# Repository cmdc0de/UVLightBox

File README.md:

# UVLightBox
UBLight Box with WIFI capabilities

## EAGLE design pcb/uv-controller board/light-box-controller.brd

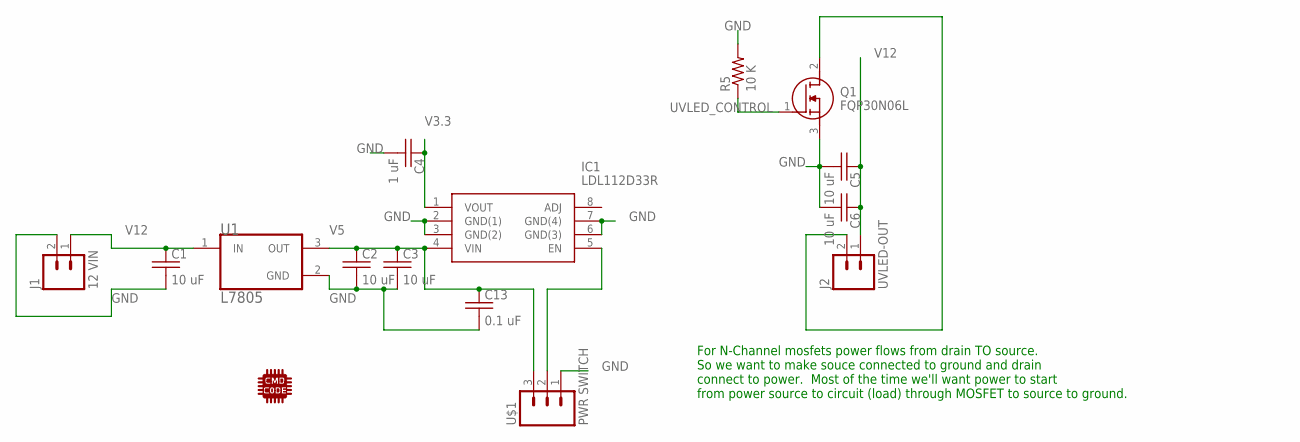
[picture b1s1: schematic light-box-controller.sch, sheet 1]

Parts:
C1, C2, C3, C5, C6: 10 uF; C0805K
C4: 1 uF; C0805K
C13: 0.1 uF; C0805K
IC1: LDL112D33R; SOIC127P600X175-8N
J1: 12 VIN; SCREWTERMINAL-5MM-2
J2: UVLED-OUT; SCREWTERMINAL-5MM-2
Q1: FQP30N06L; TO254P470X1016X2019-3P
R5: 10 K; 0805
U1: L7805; TO-220-3
U$1: PWR SWITCH; 1X03_LONGPADS
U$4: CMD_C0DE_LOGOCMD_CODE_LOGO_SILK; CMD_C0DE_LOGO_SILK

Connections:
GND: C1.2, C2.2, C3.2, C4.2, C5.2, C6.2, C13.2, IC1.2 (GND(1)), IC1.3 (GND(2)), IC1.6 (GND(3)), IC1.7 (GND(4)), J1.2, Q1.3 (S), R5.2, U1.2 (GND), U$1.1; also elsewhere on the board
unnamed: J2.2, Q1.2 (D)
unnamed: IC1.5 (EN), U$1.2
UVLED_CONTROL: Q1.1 (G), R5.1; also elsewhere on the board
V3.3: C4.1, IC1.1 (VOUT); also elsewhere on the board
V5: C2.1, C3.1, C13.1, IC1.4 (VIN), U1.3 (OUT), U$1.3
V12: C1.1, C5.1, C6.1, J1.1, J2.1, U1.1 (IN)

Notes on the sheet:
For N-Channel mosfets power flows from drain TO source. So we want to make souce connected to ground and drain connect to power. Most of the time we'll want power to start from power source to circuit (load) through MOSFET to source to ground.

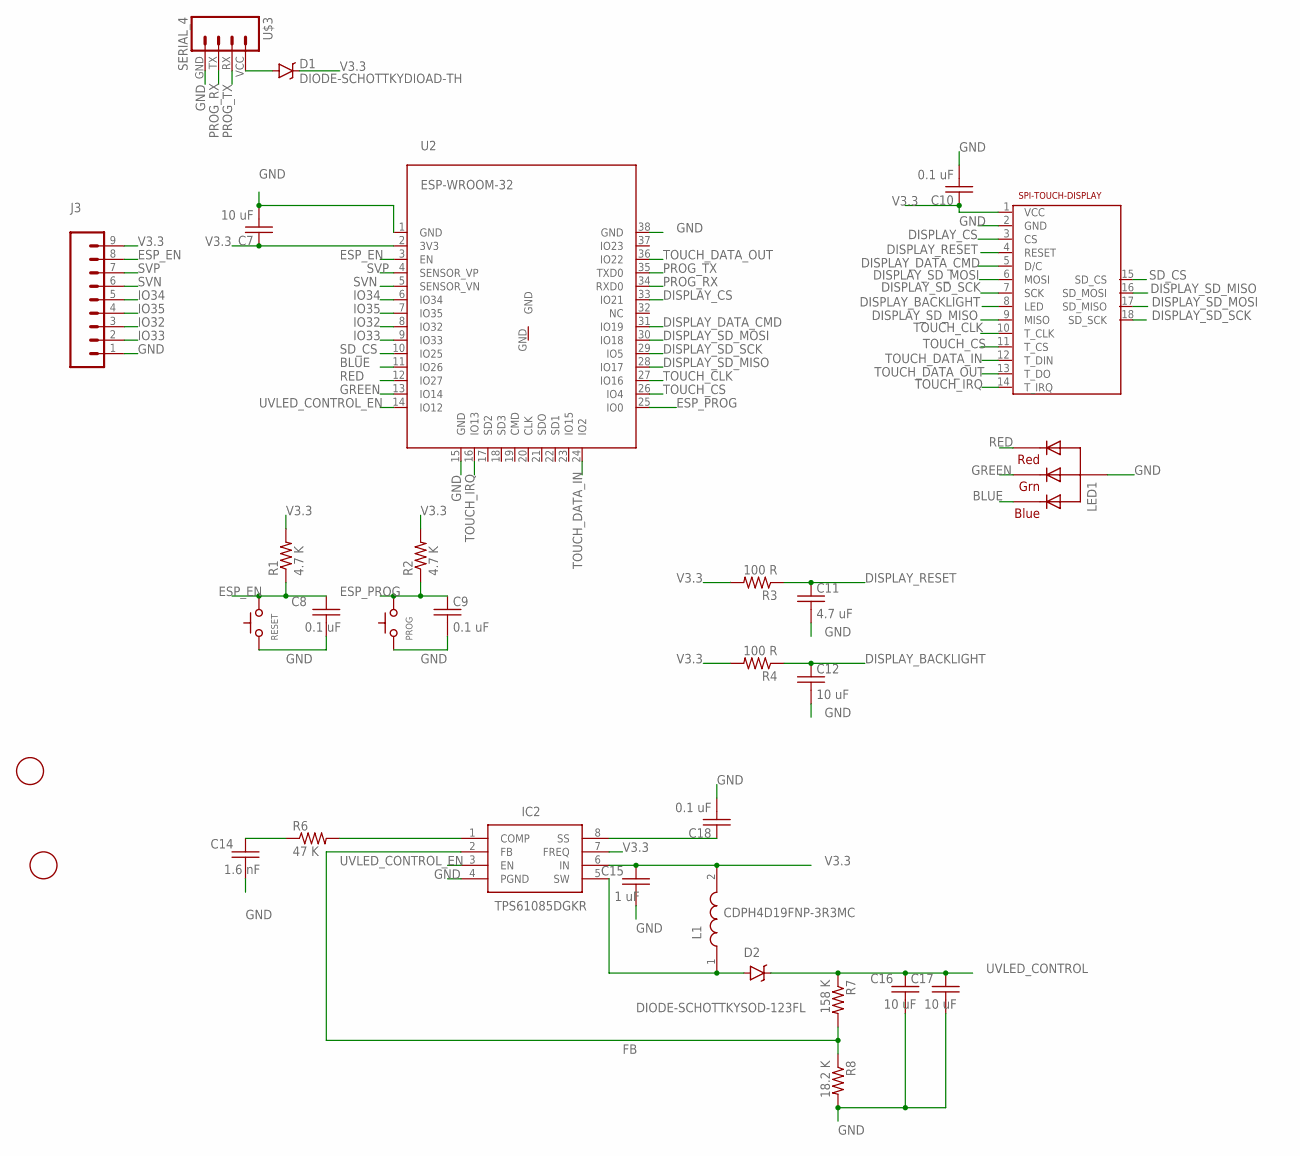
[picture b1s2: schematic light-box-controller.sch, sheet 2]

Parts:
C7, C12, C16, C17: 10 uF; C0805K
C8, C9, C10, C18: 0.1 uF; C0805K
C11: 4.7 uF; C0805K
C14: 1.6 nF; C0805K
C15: 1 uF; C0805K
D1: DIODE-SCHOTTKYDIOAD-TH; DIOAD1060W80L520D270
D2: DIODE-SCHOTTKYSOD-123FL; SOD-123FL
IC2: TPS61085DGKR; SOP65P490X110-8N
J3: M09LONGPADS; 1X09_LONGPADS
L1: CDPH4D19FNP-3R3MC; CDPH4D19FNP3R3MC
LED1: RGBLED_CA-PIRANHA; PIRANHA5MM
PROG: SWITCH_TACTILETACTILE-2PIN-NARROW; TACTILE-2PIN-NARROW
R1, R2: 4.7 K; 0805
R3, R4: 100 R; 0805
R6: 47 K; 0805
R7: 158 K; 0805
R8: 18.2 K; 0805
RESET: SWITCH_TACTILETACTILE-2PIN-NARROW; TACTILE-2PIN-NARROW
U2: ESP-WROOM-32
U$2: 2.4-SPI-TFT-TOUCH-SSD-MODULE
U$3: SERIAL_4; SERIAL_HEADER_4
U$5, U$6: FIDUCIAL; FIDUCIAL_1MM

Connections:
BLUE: LED1.1 (BLUE), U2.11 (IO26)
DISPLAY_BACKLIGHT: C12.1, R4.1, U$2.8 (LED)
DISPLAY_CS: U2.33 (IO21), U$2.3 (CS)
DISPLAY_DATA_CMD: U2.31 (IO19), U$2.5 (D/C)
DISPLAY_RESET: C11.1, R3.1, U$2.4 (RESET)
DISPLAY_SD_MISO: U2.28 (IO17), U$2.9 (MISO), U$2.16 (SD_MOSI)
DISPLAY_SD_MOSI: U2.30 (IO18), U$2.6 (MOSI), U$2.17 (SD_MISO)
DISPLAY_SD_SCK: U2.29 (IO5), U$2.7 (SCK), U$2.18 (SD_SCK)
ESP_EN: C8.1, J3.8, R1.1, RESET.P$1 (A), U2.3 (EN)
ESP_PROG: C9.1, PROG.P$1 (A), R2.1, U2.25 (IO0)
FB: IC2.2 (FB), R7.2, R8.1
GND: C7.2, C8.2, C9.2, C10.2, C11.2, C12.2, C14.2, C15.2, C16.2, C17.2, C18.2, IC2.4 (PGND), J3.1, LED1.4 (VCC), PROG.P$2 (C), R8.2, RESET.P$2 (C), U2.1 (GND), U2.15 (GND), U2.38 (GND), U$2.2 (GND), U$3.GND; also elsewhere on the board
GREEN: LED1.3 (GREEN), U2.13 (IO14)
IO32: J3.3, U2.8 (IO32)
IO33: J3.2, U2.9 (IO33)
IO34: J3.5, U2.6 (IO34)
IO35: J3.4, U2.7 (IO35)
unnamed: D1.A, U$3.VCC
unnamed: IC2.1 (COMP), R6.2
unnamed: C14.1, R6.1
unnamed: C18.1, IC2.8 (SS)
PROG_RX: U2.34 (RXD0), U$3.TX
PROG_TX: U2.35 (TXD0), U$3.RX
RED: LED1.2 (RED), U2.12 (IO27)
SD_CS: U2.10 (IO25), U$2.15 (SD_CS)
SVN: J3.6, U2.5 (SENSOR_VN)
SVP: J3.7, U2.4 (SENSOR_VP)
TOUCH_CLK: U2.27 (IO16), U$2.10 (T_CLK)
TOUCH_CS: U2.26 (IO4), U$2.11 (T_CS)
TOUCH_DATA_IN: U2.24 (IO2), U$2.12 (T_DIN)
TOUCH_DATA_OUT: U2.36 (IO22), U$2.13 (T_DO)
TOUCH_IRQ: U2.16 (IO13), U$2.14 (T_IRQ)
UVLED_BEFORE_DIODE: D2.A, IC2.5 (SW), L1.1
UVLED_CONTROL: C16.1, C17.1, D2.C, R7.1; also elsewhere on the board
UVLED_CONTROL_EN: IC2.3 (EN), U2.14 (IO12)
V3.3: C7.1, C10.1, C15.1, D1.C, IC2.6 (IN), IC2.7 (FREQ), J3.9, L1.2, R1.2, R2.2, R3.2, R4.2, U2.2 (3V3), U$2.1 (VCC); also elsewhere on the board

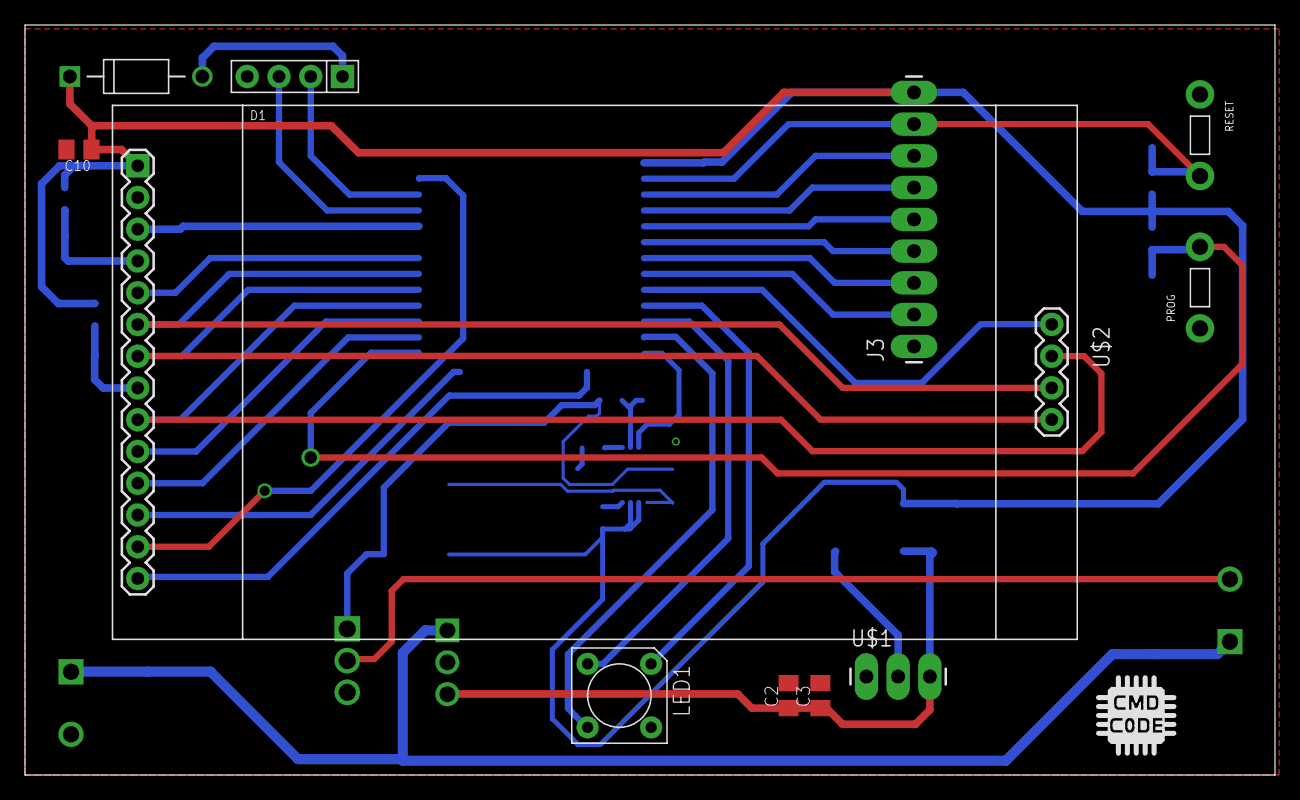
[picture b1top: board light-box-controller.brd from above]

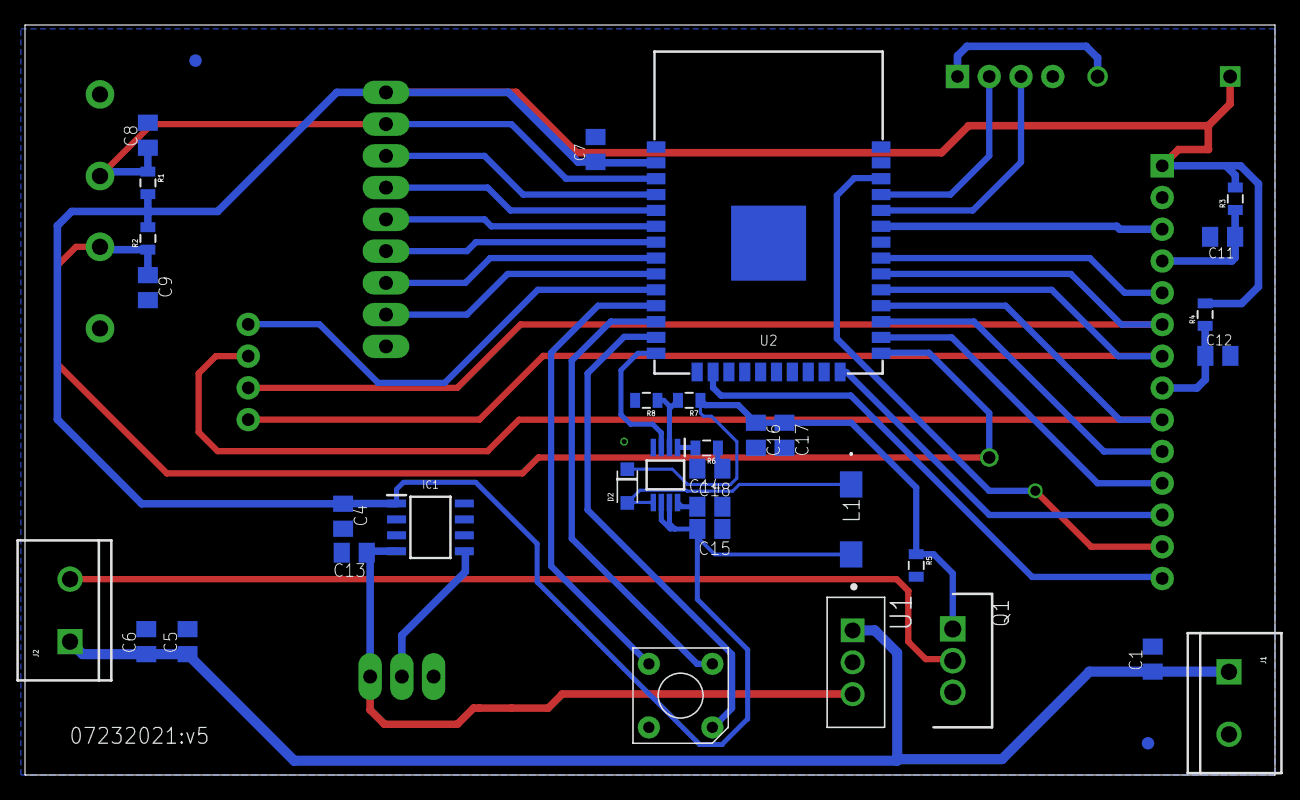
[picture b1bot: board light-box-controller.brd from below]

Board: 2 copper layers, 100.0 x 60.0 mm, 46 parts (34 on the bottom side), 40 nets.

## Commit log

2020-07-08 initial commit for board
2020-07-21 initial build working with libesp
2020-07-21 build
2020-07-21 moving back
2020-07-22 nearly compiles
2020-07-26 basics work
2020-07-28 new lib
2020-08-02 adding dcos
2020-08-09 fix memory allocation issue with new-ing memory for back buffer
2020-08-09 clean up, and a painful (as in long debugging time) that ESP32 can only allocate 160KiB of DRAM or via .bss section :(
2020-08-17 added pull down resisitor
2020-08-22 led works
2020-08-22 solder mask removal
2020-08-25 4pin led works
2020-10-04 latest esp-idf
2020-10-04 update version container
2020-11-08 update to use ground planes
2020-11-28 moving away from IO15 as I'm pretty sure its messing up the touch screen
2020-11-28 adding dxf files and updated pin config
2020-11-28 pingconfig aligns with new boards away from io15 that seems to mess up the touch chip
2021-01-05 updating to libesp32 that doesn't have the touch screen initialization bug
2021-01-06 calibartion menu now works LED is fixed
2021-01-07 start of new gui
2021-01-07 closer on new gui
2021-01-08 start of timer menu working
2021-01-25 new UI
2021-02-17 timer is closer
2021-02-24 new version of 4.2 means you have to add components/libesp
2021-03-03 closer to timer
2021-03-08 etl workin
2021-03-08 fixed multiple defs
2021-03-14 eventbus
2021-03-17 new layout for clock class / timer menu
2021-03-24 rectangle for clock
2021-04-09 countdown timer nearly works
2021-04-19 running timer works
2021-05-19 added notes to ensure I don't mess up the n-channel mosfet again. :)
2021-07-19 adding docs
2021-07-23 adding docs and added voltage multipler for mosfet gate
